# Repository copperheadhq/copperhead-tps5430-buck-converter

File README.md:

# TPS5430 12 V to 5 V Industrial Buck Converter, rev E

A compact DC/DC converter for an industrial control cabinet. It takes a 12 V supply (9 to 18 V)
and delivers a regulated 5 V at up to 3 A, built around the TI TPS5430 (500 kHz, internally
compensated) with an external Schottky catch diode. Reverse-polarity, transient and fuse
protection at the input; screw terminals at opposite edges. 60 × 40 mm, two layers, 2 oz copper.
Non-isolated: input and output share ground.

> ## ⚠ This board has never been built
>
> - **Never fabricated, never powered.** Neither rev E nor the earlier rev D has been built. Nothing
>   here has been tested on real hardware. Until bring-up passes, every number below is a design
>   value, not a measurement.
> - **Parts are checked on paper only.** Every fitted figure in [`docs/BOM.md`](docs/BOM.md) was
>   checked against its manufacturer datasheet, and the LCSC numbers and stock come from the
>   JLCPCB parts API on 2026-11-06. Stock changes; check it again before ordering.
> - **Not checked:** the gerbers in a viewer, JLCPCB's DFM report, placement rotations in
>   JLCPCB's preview, loop stability, EMC, and thermal performance at 3 A and 50 °C.
> - **One open question:** in a sustained short on the 5 V output, the TPS5430's 4 to 6 A current
>   limit could overload the 5 A catch diode D3. A shorted-output bench test decides between a
>   larger diode and an external fuse on the 5 V wiring (see [`fab/rev-e/README.md`](fab/rev-e/README.md)).
> - **The schematic title block still says "Rev: A".** The revision letter in this repository is
>   the one to go by.
>
> Passing ERC and DRC means the copper matches the schematic and a rule set. It is not evidence
> that the circuit works.

*Renders, not photographs, with every footprint populated. C7, C8, C10 and J3 are drawn for reference but are not fitted on assembled rev E boards.*

## The circuit

- **Input and protection:** a 4 A slow-blow fuse in a replaceable SMD holder (Littelfuse
  0154004.DRT), a DMP6023LE P-MOSFET against reverse polarity (no damage from -18 V) with a
  zener gate clamp, and an SMBJ18A TVS.
- **Optional EMI filter:** footprints for an input filter. Rev E ships with it bridged by FB1;
  C7 and C8 are not fitted. A footprint for a 100 µF bulk input capacitor (C10) is there for
  long field cables, also not fitted. The EN header J3 is not fitted either.
- **Buck stage:** TPS5430 with a 15 µH shielded inductor (Bourns SRP1265A-150M), a B560C
  catch diode and 10 µF + 10 µF + 100 nF input capacitors. The 10 µF C1 sits on U1's VIN and
  GND pins and closes the switching loop with D3 (about 30 mm², 6.9 nH, calculated).
- **Output:** 220 µF hybrid and 22 µF ceramic capacitors, and a 0.1 % divider (10.0 k / 3.24 k)
  setting 4.99 V, within ±3 % over the datasheet reference range. The divider senses the output
  at C5 through its own trace.
- **Interface:** Phoenix MKDS 1,5/2-5.08 screw terminals for input (J1, left edge) and output
  (J2, right edge), wire openings facing outward. A green LED shows that 5 V is present; the
  TPS5430 has no power-good output. An unfitted 2-pin header (J3), linked to EN through R5, can
  pull EN low to disable the converter. Eight test pads: VIN, 5V, SW, FB, EN and three GND,
  one of them beside SW for a short scope ground.

### What changed from rev D

- The switching loop is tighter: C1 on the regulator's pins, D3 moved up, one short input hop.
- The switch-node copper pours are gone; D3 is cooled from its ground side.
- Ground stitching is regular: a ring around the switch node, a fence along the edges and a
  grid, 170 vias.
- Curved teardrops on pads, vias and track joints.
- New: the SW ground test pad (TP8), the C10 footprint and the R5 EN link.

The design documents are in [`docs/`](docs/):

- [`BRIEF.md`](docs/BRIEF.md): what was asked for.
- [`SPEC.md`](docs/SPEC.md): the specification derived from the brief.
- [`SUBSYSTEMS.md`](docs/SUBSYSTEMS.md): the circuit, block by block.
- [`PINOUT.md`](docs/PINOUT.md): the connectors and test points.
- [`BOM.md`](docs/BOM.md): every part, with its reason and its datasheet check.
- [`DECISIONS.md`](docs/DECISIONS.md): the design's decisions.

### The board

From [`docs/BOARD-STATS.md`](docs/BOARD-STATS.md):

- **Size:** 60 x 40 mm, 1.6 mm thick, two M3 mounting holes.
- **Stackup:** two copper layers, 2 oz (70 µm), both carrying a GND pour stitched by 170 vias.
- **Parts:** 37 footprints, all on the top: 24 SMD, 3 through-hole (J1, J2, J3), and the test
  pads and mounting holes. 23 are fitted.
- **Routing:** 178 vias (0.3 and 0.4 mm drill), 13 nets, power paths 1.0 to 2.5 mm wide,
  48 teardrops and 23 curved fillets.

*Every footprint populated, including the unfitted C7, C8, C10 and J3.*

## Layout of this repository

```text
hardware/   KiCad project: schematic, board, design rules, vendored symbols and 3D models
docs/       brief, design documents, board statistics, schematic as PDF and SVG
fab/        gerbers, drill, BOM and CPL for rev E and rev D (read the README in each folder)
images/     renders of the board, not photographs
3d/         STEP, GLB and STL models
LICENSES/   full text of the licences below
```

## Building it

1. **Open:** use KiCad 10.0.6 or later on
   `hardware/tps5430-12-v-to-5-v-industrial-buck-converter.kicad_pro`. The symbols are vendored
   in `hardware/sym-lib-cache/` (through `sym-lib-table`), and the fuse and inductor models are
   in `hardware/lib/3d/`, so it opens without extra libraries.
2. **Fab files:** read [`fab/rev-e/README.md`](fab/rev-e/README.md) first. The files are the
   rev E release unchanged; the README lists what has not been checked. The rev D files stay in
   [`fab/rev-d/`](fab/rev-d/) for reference.
3. **On the JLCPCB order form:**
   - select 2 oz outer copper (the gerbers do not set it)
   - J1/J2 holes at least 1.3 mm finished
   - keep the vias tented
4. **In the placement preview:** J1's wire openings must face the left edge and J2's the right
   edge. A 180° rotation error turns them back into the board.
5. **J1 and J2 are through-hole:** they need JLCPCB through-hole assembly or hand soldering.

## Licence

| What | Licence |
|---|---|
| Hardware: everything under `hardware/`, `fab/` and `3d/` | **CERN-OHL-S-2.0** (strongly reciprocal) |
| Documentation and images: `docs/`, `images/`, `README.md` | **CC-BY-4.0** |

Full texts are in [`LICENSES/`](LICENSES/). See [`LICENSE`](LICENSE) for the per-directory
statement.

**No warranty.** CERN-OHL-S-2.0 sections 8 and 9 apply: no warranty, no liability.

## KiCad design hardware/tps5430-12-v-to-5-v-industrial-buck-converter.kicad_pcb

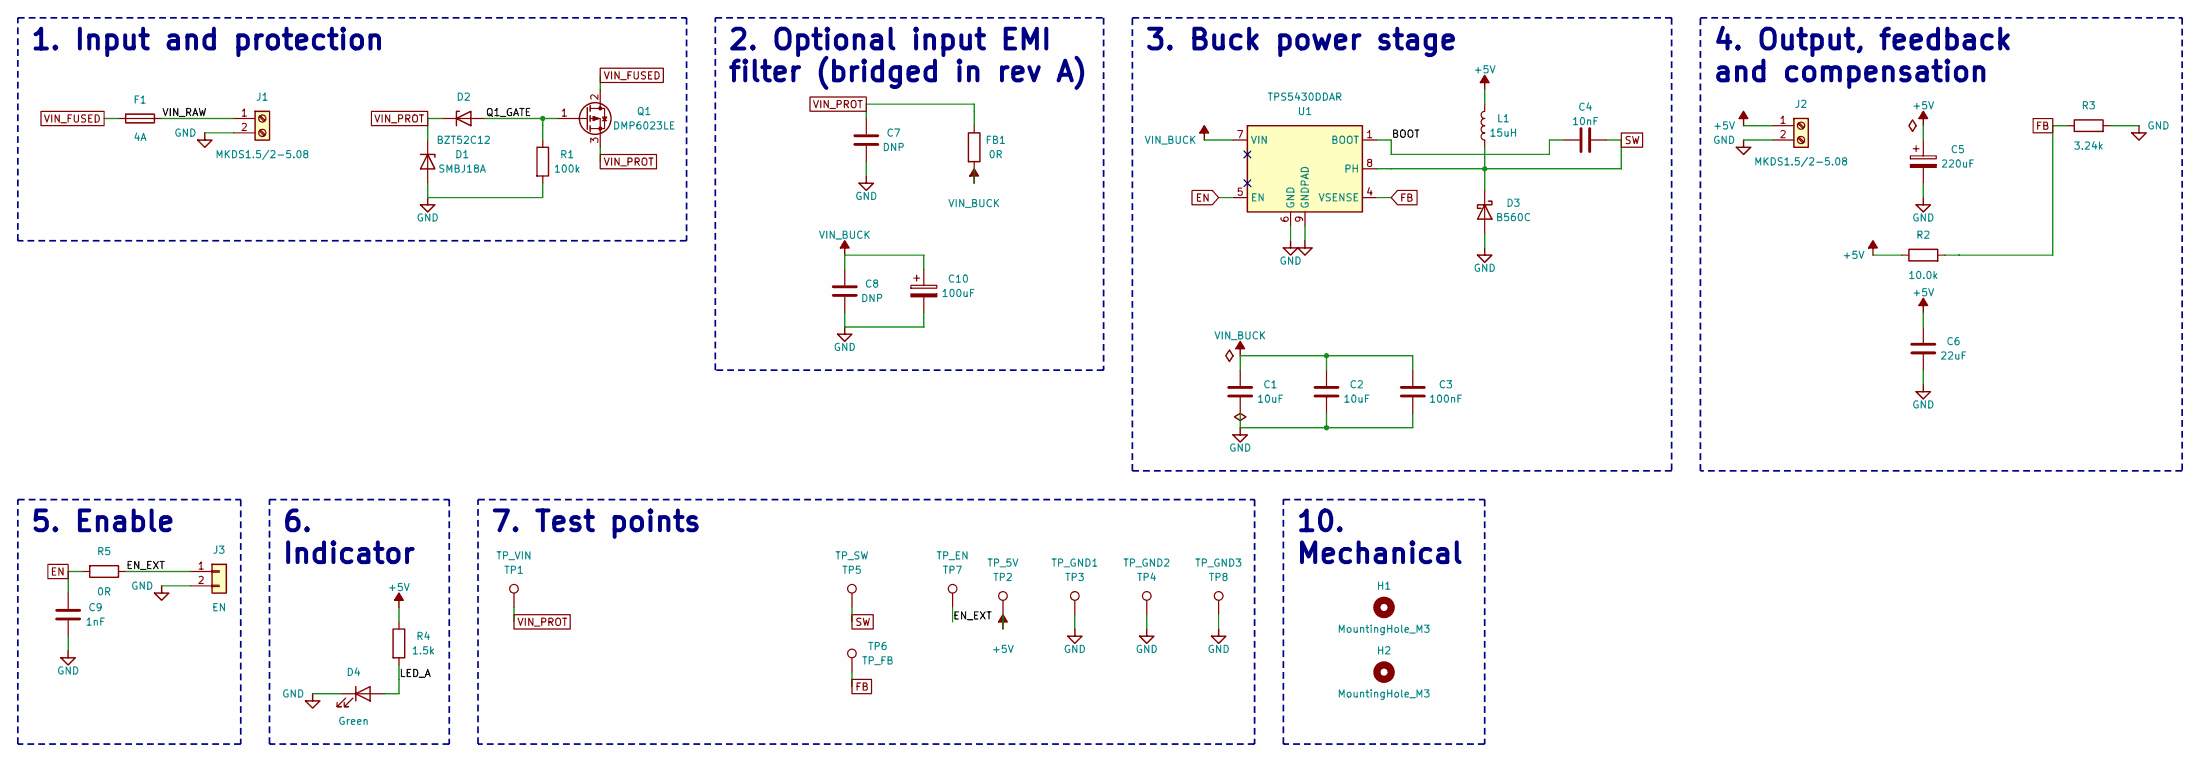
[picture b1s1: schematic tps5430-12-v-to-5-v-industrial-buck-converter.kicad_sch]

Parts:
C1, C2: 10uF; C_1210_3225Metric
C3: 100nF; C_0603_1608Metric
C4: 10nF; C_0603_1608Metric
C5: 220uF; CP_Elec_8x10
C6: 22uF; C_1210_3225Metric
C7, C8: DNP; C_1210_3225Metric
C9: 1nF; C_0603_1608Metric
C10: 100uF; CP_Elec_8x10
D1: SMBJ18A; D_SMB
D2: BZT52C12; D_SOD-123
D3: B560C; D_SMC
D4: Green; LED_0603_1608Metric
F1: 4A; Fuseholder_Littelfuse_Nano2_154x
FB1: 0R; R_2512_6332Metric
H1, H2: MountingHole_M3; MountingHole_3.2mm_M3
J1, J2: MKDS1.5/2-5.08; TerminalBlock_Phoenix_MKDS-1,5-2-5.08_1x02_P5.08mm_Horizont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
J3: EN; PinHeader_1x02_P2.54mm_Vertical
L1: 15uH; L_Bourns_SRP1245A
Q1: DMP6023LE; SOT-223-3_TabPin2
R1: 100k; R_0603_1608Metric
R2: 10.0k; R_0603_1608Metric
R3: 3.24k; R_0603_1608Metric
R4: 1.5k; R_0603_1608Metric
R5: 0R; R_0603_1608Metric
TP1: TP_VIN; TestPoint_Pad_D1.5mm
TP2: TP_5V; TestPoint_Pad_D1.5mm
TP3: TP_GND1; TestPoint_Pad_D1.5mm
TP4: TP_GND2; TestPoint_Pad_D1.5mm
TP5: TP_SW; TestPoint_Pad_1.0x1.0mm
TP6: TP_FB; TestPoint_Pad_1.0x1.0mm
TP7: TP_EN; TestPoint_Pad_D1.5mm
TP8: TP_GND3; TestPoint_Pad_1.0x1.0mm
U1: TPS5430DDAR; TI_SO-PowerPAD-8_ThermalVias

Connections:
+5V: C5.1, C6.1, J2.1, L1.2, R2.1, R4.1, TP2.1
/BOOT: C4.1, U1.1 (BOOT)
/EN_EXT: J3.1, R5.1, TP7.1
/LED_A: D4.2 (A), R4.2
/Q1_GATE: D2.2 (A), Q1.1 (G), R1.1
/VIN_RAW: F1.1, J1.1
EN: C9.1, R5.2, U1.5 (EN)
FB: R2.2, R3.1, TP6.1, U1.4 (VSENSE)
GND: C1.2, C2.2, C3.2, C5.2, C6.2, C7.2, C8.2, C9.2, C10.2, D1.2 (A), D3.2 (A), D4.1 (K), J1.2, J2.2, J3.2, R1.2, R3.2, TP3.1, TP4.1, TP8.1, U1.6 (GND), U1.9 (GNDPAD)
SW: C4.2, D3.1 (K), L1.1, TP5.1, U1.8 (PH)
VIN_BUCK: C1.1, C2.1, C3.1, C8.1, C10.1, FB1.2, U1.7 (VIN)
VIN_FUSED: F1.2, Q1.2 (D)
VIN_PROT: C7.1, D1.1 (K), D2.1 (K), FB1.1, Q1.3 (S), TP1.1

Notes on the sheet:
1. Input and protection
10. Mechanical
2. Optional input EMI filter (bridged in rev A)
3. Buck power stage
4. Output, feedback and compensation
5. Enable
6. Indicator
7. Test points

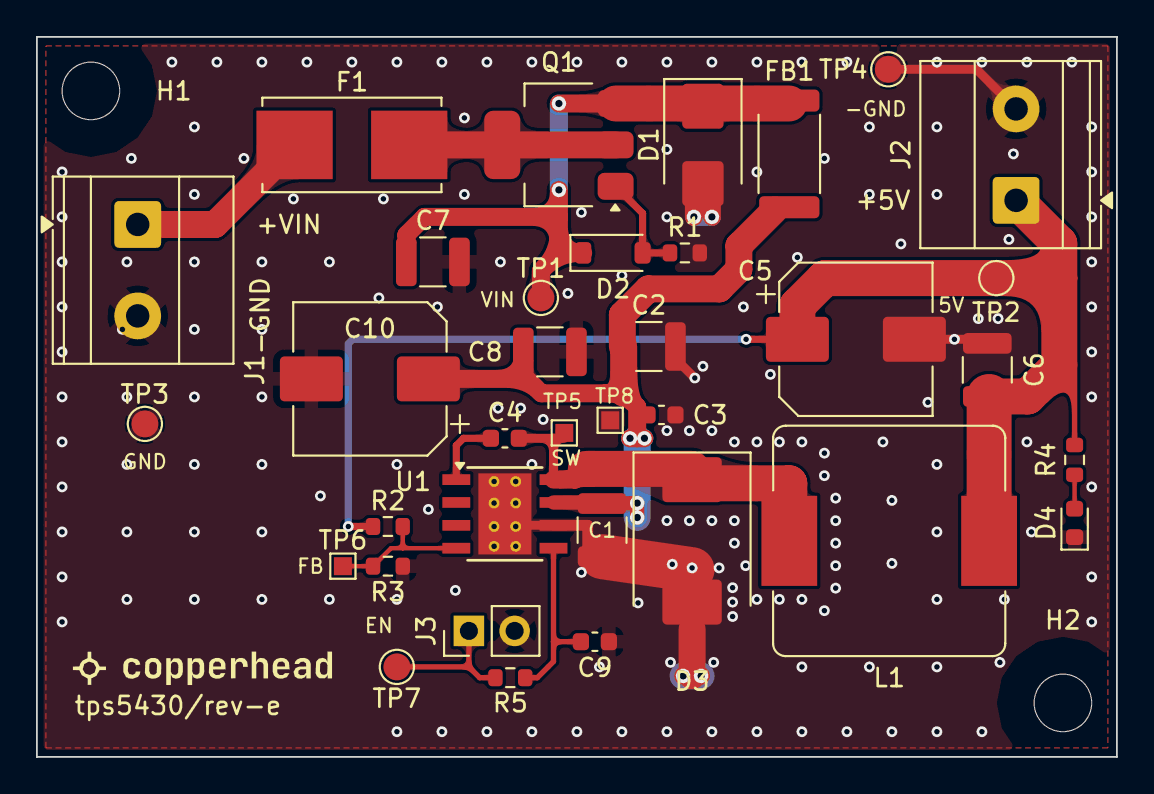
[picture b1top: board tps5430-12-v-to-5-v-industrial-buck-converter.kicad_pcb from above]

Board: 2 copper layers, 60.0 x 40.0 mm, 37 parts (0 on the bottom side), 13 nets.

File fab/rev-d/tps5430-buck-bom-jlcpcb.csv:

Comment,Designator,Footprint,LCSC Part #
10uF,"C1,C2",Capacitor_SMD:C_1210_3225Metric,C77102
100nF,C3,Capacitor_SMD:C_0603_1608Metric,C14663
10nF,C4,Capacitor_SMD:C_0603_1608Metric,C57112
220uF,C5,Capacitor_SMD:CP_Elec_8x10,C341198
22uF,C6,Capacitor_SMD:C_1210_3225Metric,C21397
DNP,"C7,C8",Capacitor_SMD:C_1210_3225Metric,
1nF,C9,Capacitor_SMD:C_0603_1608Metric,C1588
SMBJ18A,D1,Diode_SMD:D_SMB,C135055
BZT52C12,D2,Diode_SMD:D_SOD-123,C124196
B560C,D3,Diode_SMD:D_SMC,C85100
Green,D4,LED_SMD:LED_0603_1608Metric,C6848499
4A,F1,Fuse:Fuseholder_Littelfuse_Nano2_154x,C206915
0R,FB1,Resistor_SMD:R_2512_6332Metric,C346503
MKDS1.5/2-5.08,"J1,J2","TerminalBlock_Phoenix:TerminalBlock_Phoenix_MKDS-1,5-2-5.08_1x02_P5.08mm_Horizontal",C480516
EN,J3,Connector_PinHeader_2.54mm:PinHeader_1x02_P2.54mm_Vertical,
15uH,L1,Inductor_SMD:L_Bourns_SRP1245A,C189912
DMP6023LE,Q1,Package_TO_SOT_SMD:SOT-223-3_TabPin2,C154901
100k,R1,Resistor_SMD:R_0603_1608Metric,C25803
10.0k,R2,Resistor_SMD:R_0603_1608Metric,C95204
3.24k,R3,Resistor_SMD:R_0603_1608Metric,C728589
1.5k,R4,Resistor_SMD:R_0603_1608Metric,C22843
TPS5430DDAR,U1,Package_SO:TI_SO-PowerPAD-8_ThermalVias,C9864
